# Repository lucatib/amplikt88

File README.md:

# amplikt88

Mono power amplifier, schematic in KiCad 10, two sheets (PDF of both in `amplikt88.pdf`):

- `amplikt88.kicad_sch`: the amplifier (input, driver, output stage, bias trimmers).
- `power.kicad_sch`: the power supply (mains, rectifier and filter, driver rail, negative bias supply, heater centre tap).

The nets that cross between the sheets are global labels: `B_PLUS`, `B_DRV`, `B_V1`, `VBIAS_NEG`, `HEATER_A`, `HEATER_B`.

## Schematic

- **Output stage:** 2x KT88, push-pull, class AB, ultralinear (screens on the output transformer taps), adjustable fixed bias.
- **Driver:** ECC83 long-tailed pair, tail returned to the negative bias rail. The second grid is grounded through 470k, so the pair works as a phase splitter.
- **Input stage:** ECC83 section (the second section is grounded). Its cathode is not bypassed and takes the global feedback.
- **Feedback:** 120k with 18 pF in parallel, from the speaker terminal to the input stage cathode (1k to ground). It encloses all three stages, about 16 dB of loop gain.
- **Supply:** 330 V winding, bridge, C-L-C filter to about 450 V B+, separate decoupled rail for the driver, 6.3 V heaters with an artificial centre tap, about -65 V bias supply.

## Assumptions to confirm before building

The values were checked in simulation (below) but nothing has been measured on hardware.

- Output transformer 4 kohm plate-to-plate with 40 % ultralinear taps and an 8 ohm secondary, 70 W. The full specification, with what happens with other transformers, is in [docs/output-transformer.md](docs/output-transformer.md).
- Power transformer 230 V, 330 V / 300 mA HV, 6.3 V / 4.5 A, 50 V bias winding.
- The secondary must be phased so the speaker terminal is in phase with the input. If the gain rises or it oscillates, swap the secondary leads.
- Sensitivity is high: 0.24 V peak (0.17 V rms) gives 38 W. Put a volume control or an input divider in front of C3.
- Bias trimmers: the wiper goes from -65 V to about -39 V. Set both fully to the most negative end before first power-up, then raise the bias to about 60 mA per valve, measured across the 1 ohm cathode resistors (60 mV). In simulation 60 mA is at -45 V, about 77 % of the travel. The data sheet gives about -59 V for 50 mA at 460 V, so real valves will sit nearer the negative end, with only a few volts to spare: check that 60 mA can be reached and exceeded on both valves, and lower the bias winding load (R15, R16) if not.
- Capacitor voltages: with the valves cold the rectifier is unloaded and B+ rises to about 470 V, over 500 V with high mains. The reservoir capacitors are drawn as 550 V parts (or two 350 V in series with balancing resistors), the driver rail ones as 500 V with a 550 V surge rating, the coupling capacitors as 630 V.

## Safety

B+ is about 450 V and the reservoir capacitors hold charge after power-off. The 100k bleeder takes minutes to bring them down, so measure before touching.

## Notes on the schematic

- The valves are drawn as round symbols, as in period schematics. The ECC83s are KiCad's `Valve:ECC83`, in three units: two triodes and the heater. The KT88 (two units: beam tetrode and heater) and the two transformers (coils and core, polarity dots) are in `amplikt88.kicad_sym`, with the real pin numbers. KT88 pin 1 (shell) is grounded; the valve has no pin 6.
- The spare triode of V1 has grid and cathode grounded and the anode left open. ERC warns about its cathode on the ground net (a bidirectional pin next to the power flag); that warning and the one for the single `CHASSIS` label are expected.
- Short nets within a stage are drawn as wires (routed with `route_nets`, `max_length` 110 mm). The ones that cross the sheet, such as B+, the heater lines and the negative bias rail, stay as net labels.

## PCB

`amplikt88.kicad_pcb`, 212.67 x 90 mm, two layers. The board stands vertically on an L bracket, so the valves are horizontal. All parts are on the valve side. The KT88s sit at the two ends, 150.7 mm apart on the horizontal centre line: V3 on the left, turned -22.5 degrees, and V4 on the right, turned 67.5 degrees. The transformer wire pads TR2 run along the middle of the top edge (A1, UL1, CT, UL2, A2 at 6 mm pitch). The secondary pads (0, S) and the speaker terminal J3 are below them on the right. The supply wire pads J4 are 20.75 mm below TR2: B+ (pin 1) on the left, then B_DRV, B_V1, VBIAS_NEG, HEATER_A, HEATER_B, and ground (pin 7) on the right. Both ECC83s are in the lower half of the centre, the LTP (V2) under J4 and the input valve (V1) to its right, with the input header J2 on the bottom edge next to it. Each bias trimmer (Bourns 3296X, side adjust) is in the top corner on its own valve's side, RV1 next to V3 and RV2 next to V4. The 1 ohm cathode resistors are along the bottom edge (R19 left, R20 right). Four M4 mounting holes, one in each corner, 4.5 mm from the edges.

Footprints: the KT88s are on `Valve_Octal_KT88` (project library `amplikt88_board`), with the pads on the solder tabs of the socket in the JJ 3D model (25.3 mm circle, 3.2 mm holes for the 2.9 x 0.5 mm tabs, origin at the socket centre) and the courtyard set to the glass, 52 mm across; the ECC83s are on `Valve_Noval_ECC83`, the tabs of a noval PCB socket on a 17.4 mm circle with 2 mm holes, courtyard the 21.5 mm glass; the 2 W screen resistors R17 and R18 on DIN0617 (17 x 6 mm), the 1 W cathode resistors R19 and R20 on DIN0414 (11.9 x 4.5 mm). The transformer pads use `OT_7`, the supply pads `Supply_7` and the heater pads `Heater_2`. J3 is a 5.08 mm screw terminal.

Heaters are wired off the board. Each valve has a pair of wire pads (JH1 to JH4, HEATER_A and HEATER_B) next to it, and the links between them and J4 pins 5 and 6 are external wires. DRC therefore reports 3 unconnected heater items; that is intended.

Routing is one layer per net, with no vias:

- B.Cu carries only ground, as a star from J4 pin 7: 2.5 mm wide (1.2 mm into J2, whose 2.54 mm header has no room for more).
- Everything else is on F.Cu:
  - KT88 anodes to TR2 A1/A2, B+ to the centre tap and the cathodes to their 1 ohm resistors: 2.5 mm.
  - Secondary to the speaker terminal: 3 mm (3 A rms, 4.2 A peak, at 70 W into 8 ohm).
  - Heaters from each valve to its JH pads: 2 mm.
  - B_DRV, B_V1, ultralinear taps, screens and the ECC83 anodes: 1 mm.
  - Signals and the bias network: 0.5 mm.
- The one exception is `/LTP_A1` (LTP anode to C8). The parts around V1 close it in, so it takes two vias and a 13 mm jump on B.Cu.
- All tracks are at 0, 45 or 90 degrees.

Rules (net classes in `amplikt88.kicad_pro`, custom rules in `amplikt88.kicad_dru`):

- Clearance to ground copper and to the mounting holes (the screws go to the chassis) depends on the working voltage: 5 mm for B+, B_DRV, B_V1 and the ECC83 anodes (up to 470 V DC); 6.3 mm for the UL taps and screens (peaks around 650 V); 8 mm for the KT88 anodes (peaks around 900 V). The HV nets keep 2.5 mm between themselves.
- No edge touches the bracket or the chassis, so there is no HV rule at the board edge, but every track stays at least 3 mm from it.
- Minimum widths as above for the high-current and ground nets; ground only on B.Cu, every other net only on F.Cu; no vias except the named `/LTP_A1` exception.
- Pins of the same valve socket only need 1.2 mm: their spacing is set by the valve.
- No other part within 4 mm of a KT88's glass. The exceptions are R11, R13, R17 and C7 at V3 and R14, R18, R20 and C8 at V4. These were checked in 3D: they sit under the bulb, where the KT88 is only its 42 mm base up to 35 mm high (C7 and C8, the tallest, reach 26 mm). The heater pads JH1 to JH4 are also excluded from the courtyard checks against their valves; they are flat wire pads, also checked in 3D.

DRC: no errors. There are 3 unconnected heater items (intended, see above) and 3 silkscreen warnings: the KT88 socket outlines clipped at pin 1 of V3 and V4, and the RV1 value text touching the C9 outline.

Schematic parity reports the power supply parts as missing (the supply is built off this board), the four mounting holes H1, H3, H4 and H5 as extra (they have no symbol), and the `Sim.Device` fields as missing from the footprints. All three are expected.

## Simulation

`python3 spice/simulate.py` exports the SPICE netlist from the schematic with `kicad-cli` and runs ngspice on it (`--ltp ecc82`, `--rf`, `--cf` to try variants). The symbols carry `Sim.*` fields that point at `spice/amplikt88.lib`, so the same circuit also loads in KiCad's own simulator once B+, bias and a source are added. The power sheet is excluded; B+ (450 V) and the bias rail (-65 V) are ideal sources.

`python3 spice/plot.py` redraws the plots above (needs matplotlib).

Results for the schematic as drawn, 8 ohm load:

| | |
|---|---|
| Idle | 60 mA per KT88, grid -45 V; 1.5 mA per triode in the pair, anodes at 259 V |
| Loop gain at 1 kHz | 15.9 dB |
| Phase margin / gain margin, top of the band | 113 deg / 30 dB (unity at 29 kHz) |
| Phase margin / gain margin, bottom of the band | 60 deg / 22 dB (unity at 1.6 Hz) |
| Closed-loop response, -3 dB | 3 Hz to 23 kHz (-1 dB: 6 Hz to 11 kHz) |
| Output impedance at 1 kHz | 0.6 ohm (8.9 ohm without feedback) |
| 37.9 W at 1 kHz | 0.31 % THD |
| Power at 1 % THD | 77 W in the model; 70 W expected from the data sheet |
| 10 kHz square, 8 ohm / + 0.1 uF / + 1 uF | 2.3 % / 2.2 % / 2.0 % overshoot |

What the simulation changed:

- The first drawing returned the feedback to the second grid of the pair. That encloses only the pair and the output stage, and the loop gain was -2 dB, so it did nothing. It now returns to the input stage cathode.
- With 47k / 47 pF the loop gain is 24 dB and the amplifier rings with a capacitive load (85 % overshoot with 0.1 uF and 125 % with 1 uF before the compensation below, 12 % and 25 % with it) and has 33 degrees of phase margin at the bottom. 120k / 18 pF trades 8 dB of feedback for stability.
- The first values were only checked at the top of the band. At the bottom the two coupling networks and the transformer's inductance left 13 to 30 degrees of phase margin, with a peak of 7 to 13 dB at 2 to 5 Hz. C5 is now 1 uF into 1M (R5), C7 and C8 1 uF into 100k (R11, R12, the data sheet's limit for fixed bias at full dissipation), C3 100 nF: one corner far below the other two. `simulate.py` reports the margins at both ends.
- Compensation: the transformer's leakage inductance was the only thing rolling the loop off, so the margin depended on the transformer and on the load. With a low-leakage transformer and 0.1 uF across the speaker the square wave overshot 70 %, and a larger C6 made it worse. C15 (470 pF) in series with R26 (10k) between the two anodes of the pair now rolls the loop off before the transformer does: about 2 % overshoot with any of the three loads, and with transformers from 5 to 24 mH of leakage. The price is bandwidth, 23 kHz at -3 dB; with a transformer known to be good, 220 to 330 pF gives about 30 kHz.
- Drive: the data sheet asks 57 V peak on each grid for 70 W. With 1 mA per triode (33k tail) the pair ran out at about 45 V. With R8 22k and R21 15k it runs at 1.5 mA and gives 50 V at 2 % and 63 V at 4 % distortion before feedback. An ECC82 pair has more current but, with the lower loop gain (9.6 dB), 0.7 % THD at 38 W.
- With 22k from the trimmer to ground the bias range was only -65 V to -44.7 V, so -45 V sat at the end of the travel. R15 and R16 are 15k now (-65 V to -39 V).

`python3 spice/ot_study.py` repeats the bench with other output transformers (primary impedance, leakage, capacitance, inductance); its tables are in [docs/output-transformer.md](docs/output-transformer.md).

Limits: the KT88 model is fitted to one operating point (450 V, 60 mA, 11 mA/V), not to the datasheet curves; it needs less bias and gives more power than the real valve. The output transformer is a coupled-inductor model with assumed leakage (about 24 mH on the primary side) and 4 kohm plate-to-plate. Heaters, mains and the real supply are not modelled. Treat the numbers as a comparison between variants.

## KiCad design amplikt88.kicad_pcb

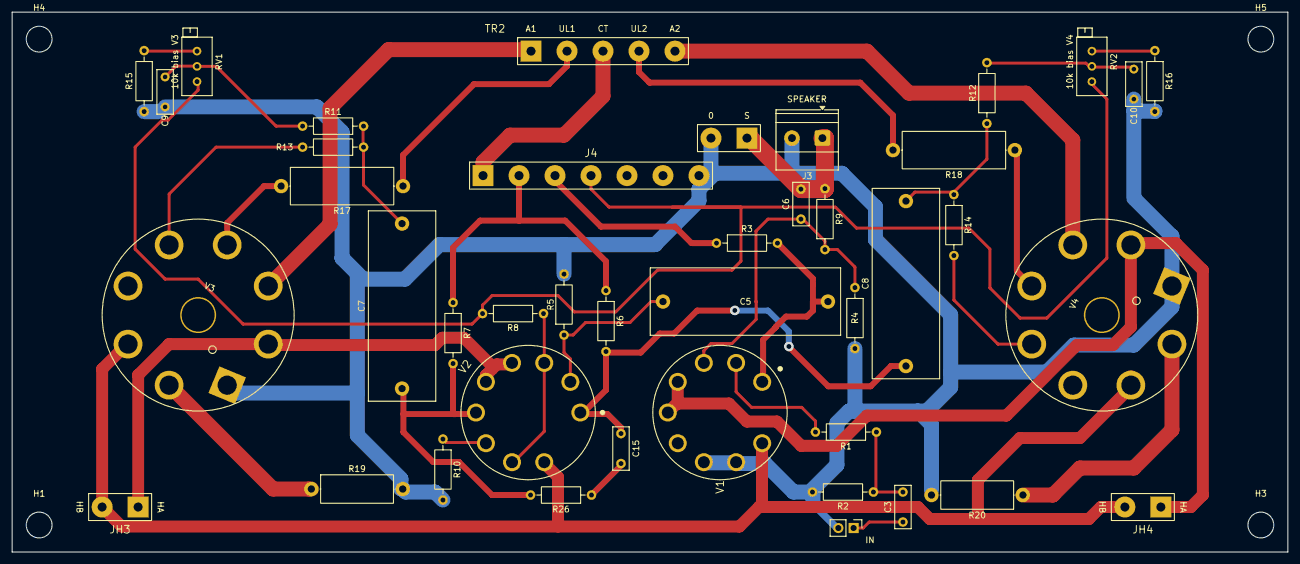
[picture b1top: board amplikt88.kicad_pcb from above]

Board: 2 copper layers, 212.7 x 90.0 mm, 45 parts (0 on the bottom side), 35 nets.

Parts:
C3: 100n; C_Disc_D7.0mm_W2.5mm_P5.00mm
C5, C7, C8: 1u 630V; C_Rect_L31.5mm_W11.0mm_P27.50mm_MKS4
C6: 18p; C_Disc_D7.0mm_W2.5mm_P5.00mm
C9, C10: 1u 100V; C_Rect_L7.2mm_W2.5mm_P5.00mm
C15: 470p 630V; C_Disc_D7.0mm_W2.5mm_P5.00mm
H1, H3, H4, H5: M4; MountingHole_4.3mm_M4
J2: IN; PinHeader_1x02_P2.54mm_Vertical
J3: SPEAKER; TerminalBlock_Phoenix_MKDS-1,5-2-5.08_1x02_P5.08mm_Horizont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
J4: OFFBOARD SUPPLY; Supply_7
JH3: HEATER V3; Heater_2
JH4: HEATER V4; Heater_2
R1, R4: 1k; R_Axial_DIN0207_L6.3mm_D2.5mm_P10.16mm_Horizontal
R2, R10: 470k; R_Axial_DIN0207_L6.3mm_D2.5mm_P10.16mm_Horizontal
R3, R11, R12: 100k; R_Axial_DIN0207_L6.3mm_D2.5mm_P10.16mm_Horizontal
R5: 1M; R_Axial_DIN0207_L6.3mm_D2.5mm_P10.16mm_Horizontal
R6, R7: 82k; R_Axial_DIN0207_L6.3mm_D2.5mm_P10.16mm_Horizontal
R8: 22k; R_Axial_DIN0207_L6.3mm_D2.5mm_P10.16mm_Horizontal
R9: 120k; R_Axial_DIN0207_L6.3mm_D2.5mm_P10.16mm_Horizontal
R13, R14: 5k; R_Axial_DIN0207_L6.3mm_D2.5mm_P10.16mm_Horizontal
R15, R16: 15k; R_Axial_DIN0207_L6.3mm_D2.5mm_P10.16mm_Horizontal
R17, R18: 470R 2W; R_Axial_DIN0617_L17.0mm_D6.0mm_P20.32mm_Horizontal
R19, R20: 1R 1W; R_Axial_DIN0414_L11.9mm_D4.5mm_P15.24mm_Horizontal
R26: 10k; R_Axial_DIN0207_L6.3mm_D2.5mm_P10.16mm_Horizontal
RV1: 10k bias V3; Potentiometer_Bourns_3296X_Horizontal
RV2: 10k bias V4; Potentiometer_Bourns_3296X_Horizontal
TR2: OT 4k a-a UL 70W; OT_7
V1, V2: ECC83; Valve_Noval_ECC83
V3, V4: KT88; Valve_Octal_KT88

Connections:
/BA_LO: R15.1, RV1.3
/BB_LO: R16.1, RV2.3
/BIAS_A: C9.1, R11.2, RV1.2
/BIAS_B: C10.1, R12.2, RV2.2
/G2_V3: R17.1, V3.4
/G2_V4: R18.1, V4.4
/G3_IN: C7.2, R11.1, R13.1
/G4_IN: C8.2, R12.1, R14.1
/IN_C: C3.2, R1.1, R2.1
/IN_RAW: C3.1, J2.1
/LTP_A1: C8.1, C15.1, R6.2, V2.1
/LTP_A2: C7.1, R7.2, R26.2, V2.6
/LTP_G1: C5.2, R5.1, V2.2
/LTP_K: R8.1, V2.3, V2.8
/LTP_STEP: C15.2, R26.1
/OT_A1: TR2.1, V3.3
/OT_A2: TR2.5, V4.3
/OT_S_HI: C6.2, J3.1, R9.2, TR2.6
/OT_UL1: R17.2, TR2.2
/OT_UL2: R18.2, TR2.4
/V1_A: C5.1, R3.2, V1.1
/V1_G: R1.2, V1.2
/V1_K: C6.1, R4.1, R9.1, V1.3
/V2_G2: R10.1, V2.7
/V3_G1: R13.2, V3.5
/V3_K: R19.1, V3.8
/V4_G1: R14.2, V4.5
/V4_K: R20.1, V4.8
B_DRV: J4.2, R6.1, R7.1
B_PLUS: J4.1, TR2.3
B_V1: J4.3, R3.1
GND: C9.2, C10.2, J2.2, J3.2, J4.7, R2.2, R4.2, R5.2, R10.2, R15.2, R16.2, R19.2, R20.2, TR2.7, V1.7, V1.8, V3.1, V4.1
HEATER_A: J4.5, JH3.1, JH4.1, V1.4, V1.5, V2.4, V2.5, V3.2, V4.2
HEATER_B: J4.6, JH3.2, JH4.2, V1.9, V2.9, V3.7, V4.7
VBIAS_NEG: J4.4, R8.2, RV1.1, RV2.1
